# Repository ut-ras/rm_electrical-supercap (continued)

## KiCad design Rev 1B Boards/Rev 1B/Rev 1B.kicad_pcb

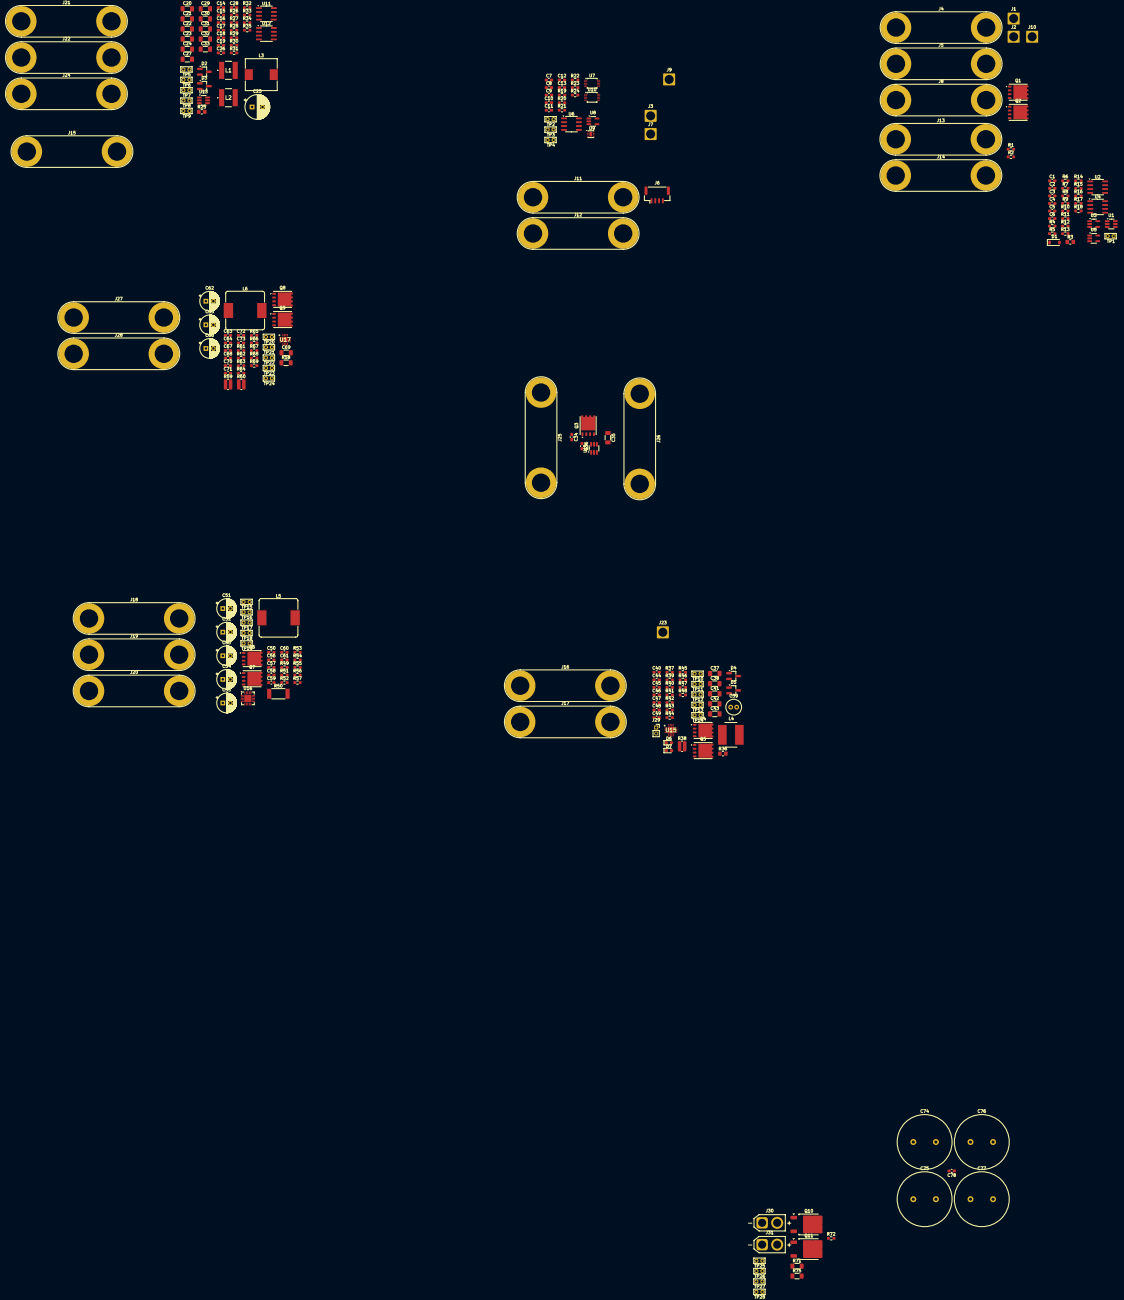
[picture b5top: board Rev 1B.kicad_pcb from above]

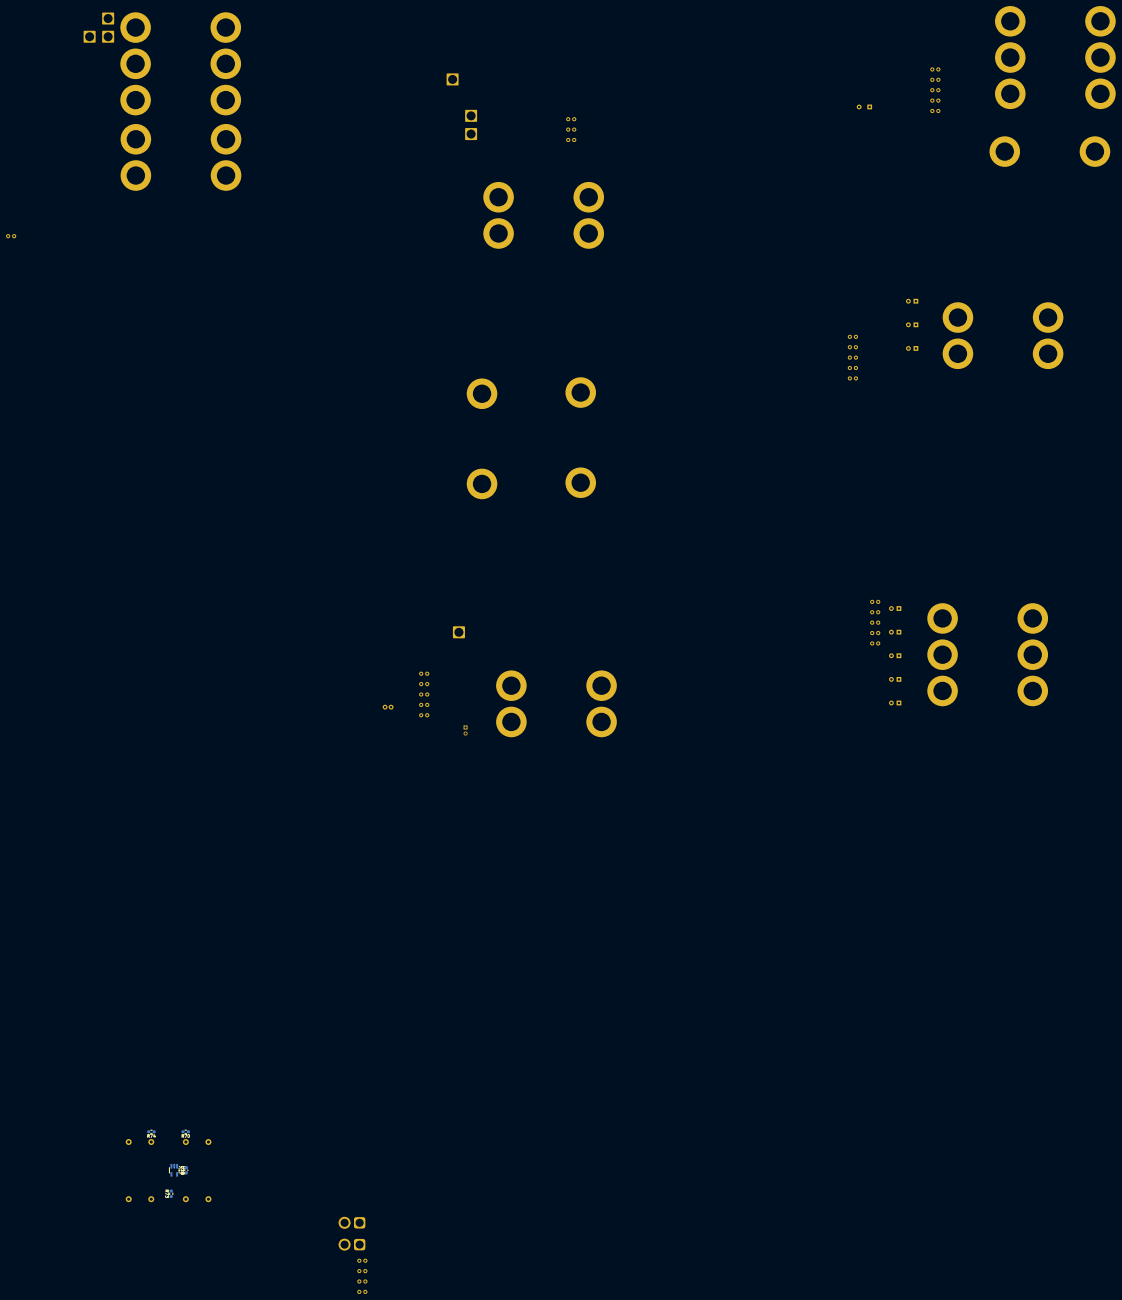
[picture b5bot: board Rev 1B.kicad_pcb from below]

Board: 2 copper layers, 255 parts (5 on the bottom side), 119 nets, no tracks yet.

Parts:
C1, C2, C3, C5, C7, C8, C9, C10, C11, C12, C26, C36, C45, C46, C49, C50, C56, C63, C64, C72, C79: 0.1u; C_0603_1608Metric_Pad1.08x0.95mm_HandSolder
C4, C6: 1000p; C_0603_1608Metric_Pad1.08x0.95mm_HandSolder
C13: 6.8u; C_0603_1608Metric_Pad1.08x0.95mm_HandSolder
C14: 82p; C_0603_1608Metric_Pad1.08x0.95mm_HandSolder
C15, C78: 100p; C_0603_1608Metric_Pad1.08x0.95mm_HandSolder
C16, C17, C40, C47, C48, C67, C68: 1u; C_0603_1608Metric_Pad1.08x0.95mm_HandSolder
C18, C19, C73: 0.01u; C_0603_1608Metric_Pad1.08x0.95mm_HandSolder
C20, C21, C22, C23, C24, C27, C29, C30, C31, C32, C33, C37, C38, C41, C42, C43, C69: 10u; C_1206_3216Metric_Pad1.33x1.80mm_HandSolder
C25: 100u; CP_Radial_D8.0mm_P3.50mm
C28: 330p; C_0603_1608Metric_Pad1.08x0.95mm_HandSolder
C34: 0.022u; C_0603_1608Metric_Pad1.08x0.95mm_HandSolder
C35: 47u; C_1206_3216Metric_Pad1.33x1.80mm_HandSolder
C39: 2.2u; C_Radial_D5.0mm_H11.0mm_P2.00mm
C44, C70: 15p; C_0603_1608Metric_Pad1.08x0.95mm_HandSolder
C51, C52, C53, C54, C55, C62, C65, C66: 220u; CP_Radial_D6.3mm_P2.50mm
C57: 200p; C_0603_1608Metric_Pad1.08x0.95mm_HandSolder
C58, C60: 0.47u; C_0603_1608Metric_Pad1.08x0.95mm_HandSolder
C59: 4.7u; C_0603_1608Metric_Pad1.08x0.95mm_HandSolder
C61: 0.015u; C_0603_1608Metric_Pad1.08x0.95mm_HandSolder
C71: 180p; C_0603_1608Metric_Pad1.08x0.95mm_HandSolder
C74, C75, C76, C77: 110; C_Radial_D18.0mm_H35.5mm_P7.50mm
D1: MMSZ4678T1G; D_SOD-123
D2, D3, D4, D5: BAT54; SOT-23_Handsoldering
D6: LTST-C193TBKT-5A; LED_0603_1608Metric_Pad1.05x0.95mm_HandSolder
D7: LTST-C193KSKT-5A; LED_0603_1608Metric_Pad1.05x0.95mm_HandSolder
J1, J2, J3, J7, J9, J10, J23: Conn_01x01_Pin; SolderWire-2.5sqmm_1x01_D2.4mm_OD3.6mm
J4, J5, J8, J11, J12, J13, J14, J15, J16, J17, J18, J19, J20, J21, J22, J24, J25, J26, J27, J28: Banana 2P; Banana_Jack_2Pin
J6: JST4_F; JST_GH_BM04B-GHS-TBT_1x04-1MP_P1.25mm_Vertical
J29: Conn_01x02_Socket; PinSocket_1x02_P2.00mm_Vertical
J30, J31: XT30_F; AMASS_XT30U-F_1x02_P5.0mm_Vertical
L1, L2: 220u; ASPIAIGS6055221MT
L3: 8.2u; L_10.4x10.4_H4.8
L4: 4.7u; L_Bourns_SRN8040TA
L5, L6: 1.8u; L_Bourns_SRP1245A
Q1, Q2, Q3, Q4, Q5, Q6, Q7, Q8, Q9: BSC059N04LS6; Infineon_PG-TDSON-8_6.15x5.15mm
Q10: 2SCR587D3; TO-252-2
Q11: 2SAR587D3; TO-252-2
R1, R2, R37, R40, R49, R51, R62, R63, R66: 0; R_0603_1608Metric_Pad0.98x0.95mm_HandSolder
R3: 0.02; R_0805_2012Metric_Pad1.20x1.40mm_HandSolder
R4, R6, R9, R13, R32: 1k; R_0603_1608Metric_Pad0.98x0.95mm_HandSolder
R5, R7, R11, R12, R15, R18, R70, R74: 1Meg; R_0603_1608Metric_Pad0.98x0.95mm_HandSolder
R8, R17, R48: 47k; R_0603_1608Metric_Pad0.98x0.95mm_HandSolder
R10, R14, R34, R61: 100k; R_0603_1608Metric_Pad0.98x0.95mm_HandSolder
R16, R42: 15k; R_0603_1608Metric_Pad0.98x0.95mm_HandSolder
R19, R20, R21, R22: 1.5k; R_0603_1608Metric_Pad0.98x0.95mm_HandSolder
R23, R30: 180k; R_0603_1608Metric_Pad0.98x0.95mm_HandSolder
R24: 220k; R_0603_1608Metric_Pad0.98x0.95mm_HandSolder
R25: 180; R_0805_2012Metric_Pad1.20x1.40mm_HandSolder
R26, R27: 1; R_0603_1608Metric_Pad0.98x0.95mm_HandSolder
R28: 1.2k; R_0603_1608Metric_Pad0.98x0.95mm_HandSolder
R29, R33, R56: 22k; R_0603_1608Metric_Pad0.98x0.95mm_HandSolder
R31: 820; R_0603_1608Metric_Pad0.98x0.95mm_HandSolder
R35: 13.7k; R_0603_1608Metric_Pad0.98x0.95mm_HandSolder
R36: 6.8; R_0805_2012Metric_Pad1.20x1.40mm_HandSolder
R38: 0.01; R_0612_1632Metric_Pad1.18x3.40mm_HandSolder
R39: 27k; R_0603_1608Metric_Pad0.98x0.95mm_HandSolder
R41, R57: 470k; R_0603_1608Metric_Pad0.98x0.95mm_HandSolder
R43, R44: 4.7k; R_0603_1608Metric_Pad0.98x0.95mm_HandSolder
R45: 9.31k; R_0603_1608Metric_Pad0.98x0.95mm_HandSolder
R46: 82k; R_0603_1608Metric_Pad0.98x0.95mm_HandSolder
R47: 430k; R_0603_1608Metric_Pad0.98x0.95mm_HandSolder
R50: 2m; R_2512_6332Metric_Pad1.40x3.35mm_HandSolder
R52: 18k; R_0603_1608Metric_Pad0.98x0.95mm_HandSolder
R53: 35.7k; R_0603_1608Metric_Pad0.98x0.95mm_HandSolder
R54: 75k; R_0603_1608Metric_Pad0.98x0.95mm_HandSolder
R55: 39k; R_0603_1608Metric_Pad0.98x0.95mm_HandSolder
R58: 47m; R_1206_3216Metric_Pad1.30x1.75mm_HandSolder
R59, R60: 1m; R_0612_1632Metric_Pad1.18x3.40mm_HandSolder
R64: 22.6k; R_0603_1608Metric_Pad0.98x0.95mm_HandSolder
R65: 330k; R_0603_1608Metric_Pad0.98x0.95mm_HandSolder
R67: 76.8k; R_0603_1608Metric_Pad0.98x0.95mm_HandSolder
R68: 30k; R_0603_1608Metric_Pad0.98x0.95mm_HandSolder
R69: 43k; R_0603_1608Metric_Pad0.98x0.95mm_HandSolder
R71, R75: 0.1; R_1206_3216Metric_Pad1.30x1.75mm_HandSolder
R72, R73: 100; R_0603_1608Metric_Pad0.98x0.95mm_HandSolder
TP1: V_{DIFF10}; TestPoint_Bridge_Pitch2.0mm_Drill0.7mm
TP2: V_{SCL}; TestPoint_Bridge_Pitch2.0mm_Drill0.7mm
TP3: V_{SDA}; TestPoint_Bridge_Pitch2.0mm_Drill0.7mm
TP4: V_{SC+BUF}; TestPoint_Bridge_Pitch2.0mm_Drill0.7mm
TP5, TP6: V_{C}; TestPoint_Bridge_Pitch2.0mm_Drill0.7mm
TP7, TP8: V_{E}; TestPoint_Bridge_Pitch2.0mm_Drill0.7mm
TP9, TP11, TP16, TP20: V_{SW}; TestPoint_Bridge_Pitch2.0mm_Drill0.7mm
TP10: V_{HIDRV}; TestPoint_Bridge_Pitch2.0mm_Drill0.7mm
TP12, TP17, TP21: V_{P}; TestPoint_Bridge_Pitch2.0mm_Drill0.7mm
TP13: V_{LODRV}; TestPoint_Bridge_Pitch2.0mm_Drill0.7mm
TP14, TP19, TP22: V_{N}; TestPoint_Bridge_Pitch2.0mm_Drill0.7mm
TP15: V_{HO}; TestPoint_Bridge_Pitch2.0mm_Drill0.7mm
TP18: V_{LO}; TestPoint_Bridge_Pitch2.0mm_Drill0.7mm
TP23: V_{LDRV}; TestPoint_Bridge_Pitch2.0mm_Drill0.7mm
TP24: V_{HDRV}; TestPoint_Bridge_Pitch2.0mm_Drill0.7mm
TP25: V_{OUT}; TestPoint_Bridge_Pitch2.0mm_Drill0.7mm
TP26: V_{CAP}; TestPoint_Bridge_Pitch2.0mm_Drill0.7mm
TP27: V_{MID}; TestPoint_Bridge_Pitch2.0mm_Drill0.7mm
TP28: V_{REF}; TestPoint_Bridge_Pitch2.0mm_Drill0.7mm
U1: MAX4073T; SOT-23-6_Handsoldering
U2, U4: OPA551U; SOIC-8_3.9x4.9mm_P1.27mm
U3, U5, U8, U18: TLV9301xDBV; SOT-23-5_HandSoldering
U6: ISO164xB; SOIC-8_3.9x4.9mm_P1.27mm
U7, U10: ADS1014IDGS; TSSOP-10_3x3mm_P0.5mm
U9: DAC53401; WSON-8-1EP_2x2mm_P0.5mm_EP0.9x1.6mm
U11, U12: MC34063A; SOIC-8_3.9x4.9mm_P1.27mm
U13: TPS54302; SOT-23-6_Handsoldering
U14: LM74700; SOT-23-6_Handsoldering
U15: BQ24640; QFN50P350X350X100-17N-D
U16: LM5123-Q1; Texas_RGP0020H_VQFN-20-1EP_4x4mm_P0.5mm_EP2.4x2.4mm
U17: TPS43061; Texas_S-PWQFN-N16

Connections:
+3V3: C7.1, C8.2, C11.2, C12.2, C18.2, C20.1, J12.1, J15.1, L2.2, R21.1, R22.1, R28.2, U6.8 (VCC2), U7.8 (VDD), U9.1 (A0), U9.6 (VDD), U10.1 (ADDR), U10.8 (VDD)
+5V: C28.1, C29.1, C30.1, C31.1, C32.1, C33.1, J22.1, L3.2, R34.1
+24V: C1.1, C5.1, C10.2, J8.1, J11.1, J20.1, Q1.1 (S), Q1.2 (S), Q1.3 (S), R3.2, U1.5 (RS-), U3.5 (V+), U5.5 (V+), U8.5 (V+), U16.8 (BIAS)
/+3V3_{DEV}: C9.2, J6.1, R19.1, R20.1, U6.1 (VCC1)
/+4.4V_{SCAP}_BYPASS: C35.1, J26.1, Q3.5 (D), U14.4 (CATHODE)
/+4.4V_{SCAP}_IN: C62.1, C63.1, J27.1, R58.1, R59.1, TP21.1, U17.6 (ISNS+), U17.7 (VIN)
/+4.4V_{SCAP}_OUT: C50.1, C51.1, C52.1, C53.1, C54.1, C55.1, J19.1, Q6.5 (D), U16.3 (VOUT)
/+6V_{SCAP}_ADC: J7.1, R23.1
/+6V_{SCAP}_BYPASS: C34.1, C36.1, J25.1, Q3.1 (S), Q3.2 (S), Q3.3 (S), U14.3 (EN), U14.6 (ANODE)
/+6V_{SCAP}_IN: J18.1, R50.1, R55.1, TP17.1, U16.1 (CSP)
/+6V_{SCAP}_OUT: C41.1, C42.1, C43.1, C44.1, C46.2, J17.1, R38.2, R39.1, TP14.1, U15.9 (SRN)
/+24V_CAP_IN: J14.1, Q2.1 (S), Q2.2 (S), Q2.3 (S)
/+24V_CAP_OUT: C65.1, C66.1, C67.1, C68.1, C70.1, J28.1, Q8.5 (D), R65.1
/+24_IN: C37.1, C38.1, C39.1, D4.1 (A), J4.1, J16.1, Q4.5 (D), R3.1, R43.1, R44.1, U1.3 (Vcc), U1.4 (RS+)
/+24_MERGED: J5.1, Q1.5 (D), Q2.5 (D)
/+24_{MiniPC}: C16.1, C17.1, C25.1, C27.1, J21.1, R26.1, R27.1, U11.6 (VCC), U12.6 (VCC), U13.3 (VIN)
/BAT_CTRL: C4.2, R1.1, R7.2, U2.6
/BAT_CTRL_R: Q1.4 (G), R1.2
/CAP_CTRL: C6.2, R15.2, U4.6
/CAP_CTRL_R: Q2.4 (G), R2.2
/CHARGE_EN_IN: J23.1, U15.2 (CE)
/CHARGE_EN_OUT: D1.2 (A), J10.1, R16.2
/CURR_IN: J9.1, U7.4 (AIN0)
/CURR_OUT: J2.1, R6.1, R9.1, R14.1, U3.1, U3.4 (-)
/Current Sense/1+: R4.2, R5.2, U2.3 (+)
/Current Sense/1-: C4.1, R6.2, R7.1, U2.2 (-)
/Current Sense/2+: R9.2, R11.2, U4.3 (+)
/Current Sense/2-: C6.1, R13.2, R15.1, U4.2 (-)
/Current Sense/3+: R10.2, R12.2, U5.3 (+)
/Current Sense/3-: R14.2, R18.1, U5.4 (-)
/Current Sense/CURR_{RAW}: U1.6 (OUT), U3.3 (+)
/Current Sense/DIFF10: D1.1 (K), R18.2, TP1.1, U5.1
/Current Sense/FLAG_{1}: R8.1, U2.8 (Flag)
/Current Sense/FLAG_{2}: R17.1, U4.8 (Flag)
/Dev Board Interface/CAP_{1}: C13.1, U9.4 (CAP)
/Dev Board Interface/SCL_{INT}: R21.2, TP2.1, U6.6 (SCL2), U7.10 (SCL), U9.2 (SCL), U10.10 (SCL)
/Dev Board Interface/SDA_{INT}: R22.2, TP3.1, U6.7 (SDA2), U7.9 (SDA), U9.3 (SDA), U10.9 (SDA)
/Dev Board Interface/V_{SC}_BUF: TP4.1, U8.1, U8.4 (-), U10.4 (AIN0)
/Dev Board Interface/V_{SC}_scaled: R23.2, R24.1, U8.3 (+)
/Housekeeping Power Supplies/3V3_COMP: C18.1, R28.1, R30.1, R31.1, U11.5 (COMP-)
/Housekeeping Power Supplies/3V3_CT: C14.1, U11.3 (CT)
/Housekeeping Power Supplies/3V3_SW: D3.3 (K), L2.1, TP8.1, U11.2 (SE)
/Housekeeping Power Supplies/3V3_VC: R26.2, TP5.1, U11.1 (SC), U11.7 (I_{PK}), U11.8 (DC)
/Housekeeping Power Supplies/30V_COMP: C19.1, R29.1, R32.1, R33.1, U12.5 (COMP-)
/Housekeeping Power Supplies/30V_CT: C15.1, U12.3 (CT)
/Housekeeping Power Supplies/30V_DC: R25.2, U12.8 (DC)
/Housekeeping Power Supplies/30V_SW: D2.1 (A), L1.2, TP7.1, U12.1 (SC)
/Housekeeping Power Supplies/30V_VC: L1.1, R25.1, R27.2, TP6.1, U12.7 (I_{PK})
/Housekeeping Power Supplies/BOOT: C26.1, U13.6 (BOOT)
/Housekeeping Power Supplies/FB: C28.2, R34.2, R35.1, U13.4 (FB)
/Housekeeping Power Supplies/SW: C26.2, L3.1, TP9.1, U13.2 (SW)
/Ideal Diode/GATE: Q3.4 (G), U14.5 (GATE)
/Ideal Diode/VCAP: C36.2, U14.1 (VCAP)
/Input Buck & Charger/BTST: C49.1, D5.3 (K), U15.16 (BTST)
/Input Buck & Charger/HIDRV: R37.1, U15.15 (HIDRV)
/Input Buck & Charger/HIDRV_R: Q4.4 (G), R37.2, TP10.1
/Input Buck & Charger/ISET: R46.2, R48.1, U15.7 (ISET)
/Input Buck & Charger/LODRV: R40.1, U15.13 (LODRV)
/Input Buck & Charger/LODRV_R: Q5.4 (G), R40.2, TP13.1
/Input Buck & Charger/PH: C49.2, L4.1, Q4.1 (S), Q4.2 (S), Q4.3 (S), Q5.5 (D), TP11.1, U15.14 (PH)
/Input Buck & Charger/REGN: C48.1, D5.1 (A), U15.12 (REGN)
/Input Buck & Charger/SRP: C45.1, C46.1, L4.2, R38.1, TP12.1, U15.10 (SRP)
/Input Buck & Charger/STAT: D6.1 (K), U15.3 (STAT)
/Input Buck & Charger/STAT_D: D6.2 (A), R43.2
/Input Buck & Charger/TS: J29.1, R45.2, R47.1, U15.4 (TS)
/Input Buck & Charger/VCC: C40.1, R36.2, U15.1 (VCC)
/Input Buck & Charger/VCC_R: D4.3 (K), R36.1
/Input Buck & Charger/VFB: C44.2, R39.2, R41.1, R42.1, U15.8 (VFB)
/Input Buck & Charger/VREF: C47.1, R45.1, R46.1, U15.6 (VREF)
/Input Buck & Charger/~PG: D7.1 (K), U15.5 (~PG)
/Input Buck & Charger/~PG_D: D7.2 (A), R44.2
/Output Boost (Stage 1)/COMP: C57.1, R52.1, U16.20 (COMP)
/Output Boost (Stage 1)/COMP_RC: C61.1, R52.2
/Output Boost (Stage 1)/CSN: L5.1, R50.2, TP19.1, U16.2 (CSN)
/Output Boost (Stage 1)/HB: C56.1, U16.7 (HB)
/Output Boost (Stage 1)/HO: R49.2, U16.5 (HO)
/Output Boost (Stage 1)/HO_R: Q6.4 (G), R49.1, TP15.1
/Output Boost (Stage 1)/LO: R51.2, U16.11 (LO)
/Output Boost (Stage 1)/LO_R: Q7.4 (G), R51.1, TP18.1
/Output Boost (Stage 1)/RT: R53.1, U16.15 (RT)
/Output Boost (Stage 1)/SS: C58.1, U16.17 (SS)
/Output Boost (Stage 1)/SW: C56.2, L5.2, Q6.1 (S), Q6.2 (S), Q6.3 (S), Q7.5 (D), TP16.1, U16.6 (SW)
/Output Boost (Stage 1)/TRK: R54.2, R56.1, U16.18 (TRK)
/Output Boost (Stage 1)/UVLO: R55.2, R57.1, U16.13 (UVLO)
/Output Boost (Stage 1)/VCC: C59.1, U16.9 (VCC)
/Output Boost (Stage 1)/VREF: C60.1, R54.1, U16.16 (VREF)
/Output Boost (Stage 2)/BOOT: C64.2, U17.11 (BOOT)
/Output Boost (Stage 2)/COMP: C71.1, R64.1, U17.3 (COMP)
/Output Boost (Stage 2)/COMP_R: C73.1, R64.2
/Output Boost (Stage 2)/FB: C70.2, R65.2, R68.1, R69.1, U17.4 (FB)
/Output Boost (Stage 2)/HDRV: R66.1, U17.13 (HDRV)
/Output Boost (Stage 2)/HDRV_R: Q8.4 (G), R66.2, TP24.1
/Output Boost (Stage 2)/IN_R: R59.2, R60.1
/Output Boost (Stage 2)/ISNS-: L6.1, R58.2, R60.2, TP22.1, U17.5 (ISNS-)
/Output Boost (Stage 2)/LDRV: R63.1, U17.8 (LDRV)
/Output Boost (Stage 2)/LDRV_R: Q9.4 (G), R63.2, TP23.1
/Output Boost (Stage 2)/PGND: C69.2, Q9.1 (S), Q9.2 (S), Q9.3 (S), R62.1, U17.9 (PGND)
/Output Boost (Stage 2)/PGOOD: R61.2, U17.14 (PGOOD)
/Output Boost (Stage 2)/RT: R67.1, U17.1 (RT)
/Output Boost (Stage 2)/SS: C72.1, U17.2 (SS)
/Output Boost (Stage 2)/SW: C64.1, L6.2, Q8.1 (S), Q8.2 (S), Q8.3 (S), Q9.5 (D), TP20.1, U17.12 (SW)
/Output Boost (Stage 2)/VCC: C69.1, R61.1, U17.10 (VCC)
/POW_LIMIT_IN: J1.1, R4.1, R10.1, R13.1
/POW_LIMIT_OUT: J3.1, U9.7 (FB), U9.8 (OUT)
/SCL_{IN}: J6.2, R20.2, U6.3 (SCL1)
/SDA_{IN}: J6.3, R19.2, U6.2 (SDA1)
/Supercapacitors/LOWER_R: Q11.3 (E), R75.2
/Supercapacitors/MID: C74.2, C75.2, C76.1, C77.1, R71.2, R72.2, R73.1, R75.1, TP27.1
/Supercapacitors/OP_OUT: C78.2, Q10.1 (B), Q11.1 (B), R72.1, TP25.1, U18.1
/Supercapacitors/REF: R70.2, R74.1, TP28.1, U18.3 (+)
/Supercapacitors/UPPER_R: Q10.3 (E), R71.1
/Supercapacitors/V-: C78.1, R73.2, U18.4 (-)
/Supercapacitors/V_{CAP}: C74.1, C75.1, J30.1, R70.1, TP26.1
/Supercapacitors/V_{CC}: C79.1, J31.1, Q10.2 (C), U18.5 (V+)
GND: C2.2, C3.2, C7.2, C8.1, C11.1, C12.1, C13.2, C14.2, C15.2, C16.2, C17.2, C20.2, C21.2, C22.2, C23.2, C24.2, C25.2, C27.2, C29.2, C30.2, C31.2, C32.2, C33.2, D3.1 (A), J11.2, J12.2, J13.2, J15.2, J20.2, J21.2, J24.2, R8.2, R17.2, R24.2, R30.2, R31.2, R32.2, R33.2, R35.2, U2.1 (V-), U2.4 (V-), U2.5 (V-), U4.1 (V-), U4.4 (V-), U4.5 (V-), U6.5 (GND2), U7.1 (ADDR), U7.3 (GND), U9.5 (AGND), U9.9 (PAD), U10.3 (GND), U11.4 (GND), U12.2 (SE), U12.4 (GND), U13.1 (GND)
GND1: C76.2, C77.2, C79.2, J30.2, J31.2, Q11.2 (C), R74.2, U18.2 (V-)
GNDD: C9.1, J6.4, U6.4 (GND1)
GNDPWR: C1.2, C5.2, C10.1, C34.2, C35.2, C37.2, C38.2, C39.2, C40.2, C41.2, C42.2, C43.2, C45.2, C47.2, C48.2, C50.2, C51.2, C52.2, C53.2, C54.2, C55.2, C57.2, C58.2, C59.2, C60.2, C61.2, C62.2, C63.2, C65.2, C66.2, C67.2, C68.2, C71.2, C72.2, C73.2, J4.2, J5.2, J8.2, J14.2, J16.2, J17.2, J18.2, J19.2, J22.2, J25.2, J26.2, J27.2, J28.2, J29.2, Q5.1 (S), Q5.2 (S), Q5.3 (S), Q7.1 (S), Q7.2 (S), Q7.3 (S), R5.1, R11.1, R12.1, R16.1, R41.2, R42.2, R47.2, R48.2, R53.2, R56.2, R57.2, R62.2, R67.2, R68.2, R69.2, U1.1 (GND), U1.2 (GND), U3.2 (V-), U5.2 (V-), U7.5 (AIN1), U8.2 (V-), U10.5 (AIN1), U14.2 (GND), U15.11 (GND), U15.17 (PAD), U16.10 (PGND), U16.14 (SYNC/DITHER), U16.19 (AGND), U16.21 (EP), U17.16 (AGND), U17.17 (PAD)
VCC: C2.1, C3.1, C19.2, C21.1, C22.1, C23.1, C24.1, D2.3 (K), J13.1, J24.1, R29.2, U2.7 (V+), U4.7 (V+)
